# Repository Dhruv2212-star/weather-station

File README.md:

# Assembly image (what it will look like inside)

## Schematic (connections of the components)

## PCB tracings 

# What is this rediculous looking thing?? 
It is a really cheap and simple Weather station! it shows you data of your surrounding area such as temp, humidity, AQI  
i made it as a challenge to make a weather station that shows data not just on a LCD but on your phone from YOUR surrounding, not some  
sensor miles away from your surrounding.  
# Firmware 
since this uses ESP32, simply flash the firmware onto the board 
# ussage
connect it to the Wifi and you should be able to be see the data as a webpage on it's IP.  

# BOM 
| Reference | Qty | Value | DNP | Exclude from BOM | Exclude from Board | Footprint | Datasheet |
|---|---:|---|---|---|---|---|---|
| C1,C2 | 2 | 4.7 µF | | | | Capacitor_SMD:C_0805_2012Metric | |
| C3,C4,C5,C6 | 4 | 10 µF | | | | Capacitor_SMD:C_0805_2012Metric | |
| D1 | 1 | STATUS LED | | | | LED_THT:LED_D5.0mm | |
| J1 | 1 | USB_C_Receptacle_USB2.0_16P | | | | Connector_USB:USB_C_Receptacle_GCT_USB4105-xx-A_16P_TopMnt_Horizontal | [USB Type-C Specification](https://www.usb.org/sites/default/files/documents/usb_type-c.zip) |
| J2 | 1 | TPS61023 | | | | Connector_PinHeader_2.54mm:PinHeader_1x04_P2.54mm_Vertical | |
| J3 | 1 | Battery | | | | Connector_PinHeader_2.54mm:PinHeader_1x02_P2.54mm_Vertical | |
| J4 | 1 | BME280 | | | | Connector_PinHeader_2.54mm:PinHeader_1x04_P2.54mm_Vertical | |
| J5 | 1 | PMS5003 | | | | Connector_JST:JST_GH_BM08B-GHS-TBT_1x08-1MP_P1.25mm_Vertical | |
| R1 | 1 | 330 Ω | | | | Resistor_THT:R_Axial_DIN0207_L6.3mm_D2.5mm_P10.16mm_Horizontal | |
| R2 | 1 | 2 kΩ | | | | Resistor_SMD:R_0805_2012Metric | |
| R3,R4 | 2 | 5.1 kΩ | | | | Resistor_SMD:R_0805_2012Metric | |
| SW1,SW2,SW3 | 3 | SW_Push | | | | Button_Switch_THT:SW_PUSH_6mm | |
| U1 | 1 | ESP32-WROOM-32 | | | | ESP32 symbol and footprint:MODULE_ESP32-DEVKITC | [ESP32-WROOM-32 Datasheet](https://www.espressif.com/sites/default/files/documentation/esp32-wroom-32_datasheet_en.pdf) |
| U2 | 1 | MCP73831-2-OT | | | | Package_TO_SOT_SMD:SOT-23-5 | [MCP73831 Datasheet](http://ww1.microchip.com/downloads/en/DeviceDoc/20001984g.pdf) |
| U3 | 1 | AP2112K-3.3 | | | | Package_TO_SOT_SMD:SOT-23-5 | [AP2112K Datasheet](https://www.diodes.com/assets/Datasheets/AP2112.pdf) |

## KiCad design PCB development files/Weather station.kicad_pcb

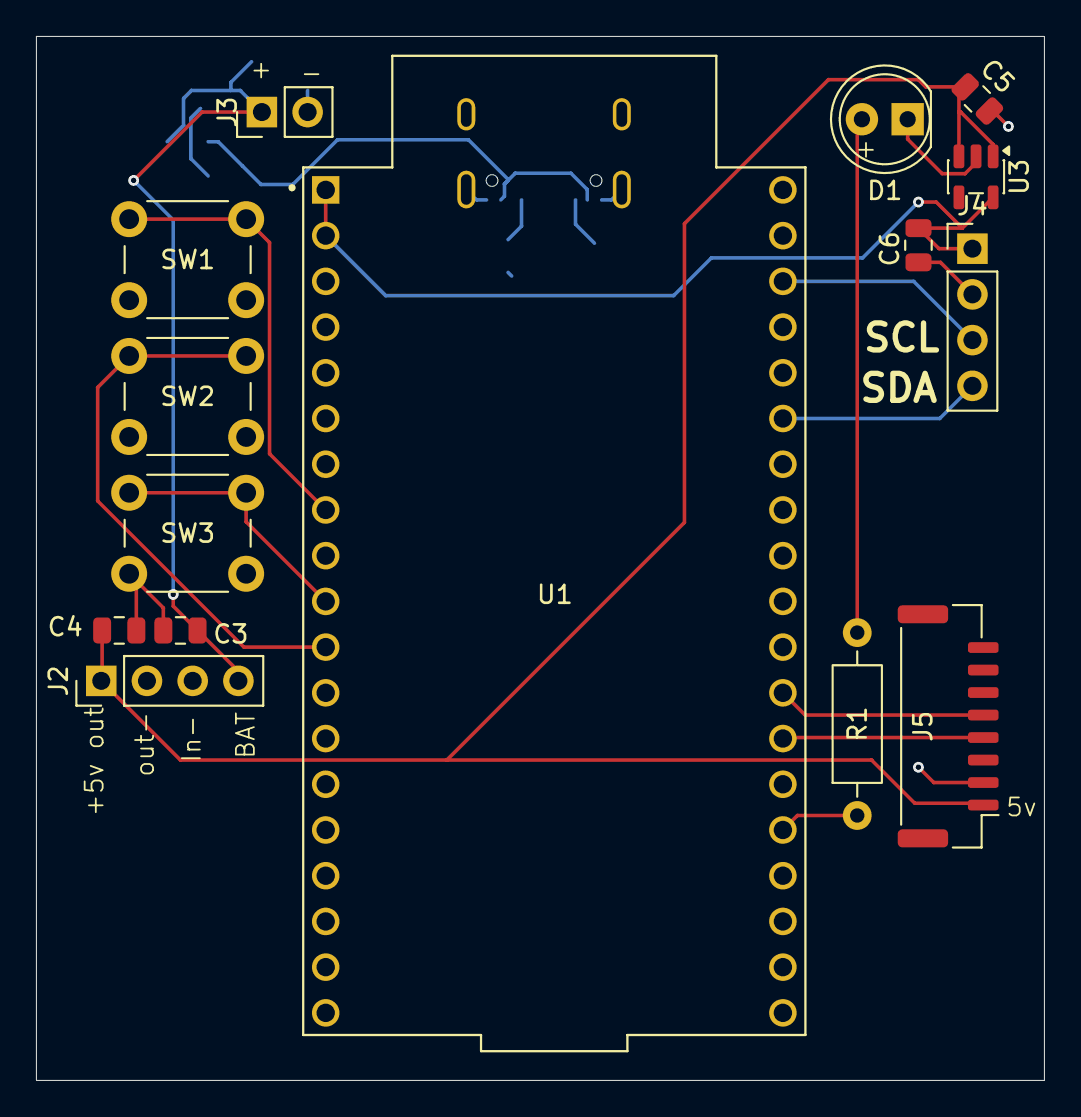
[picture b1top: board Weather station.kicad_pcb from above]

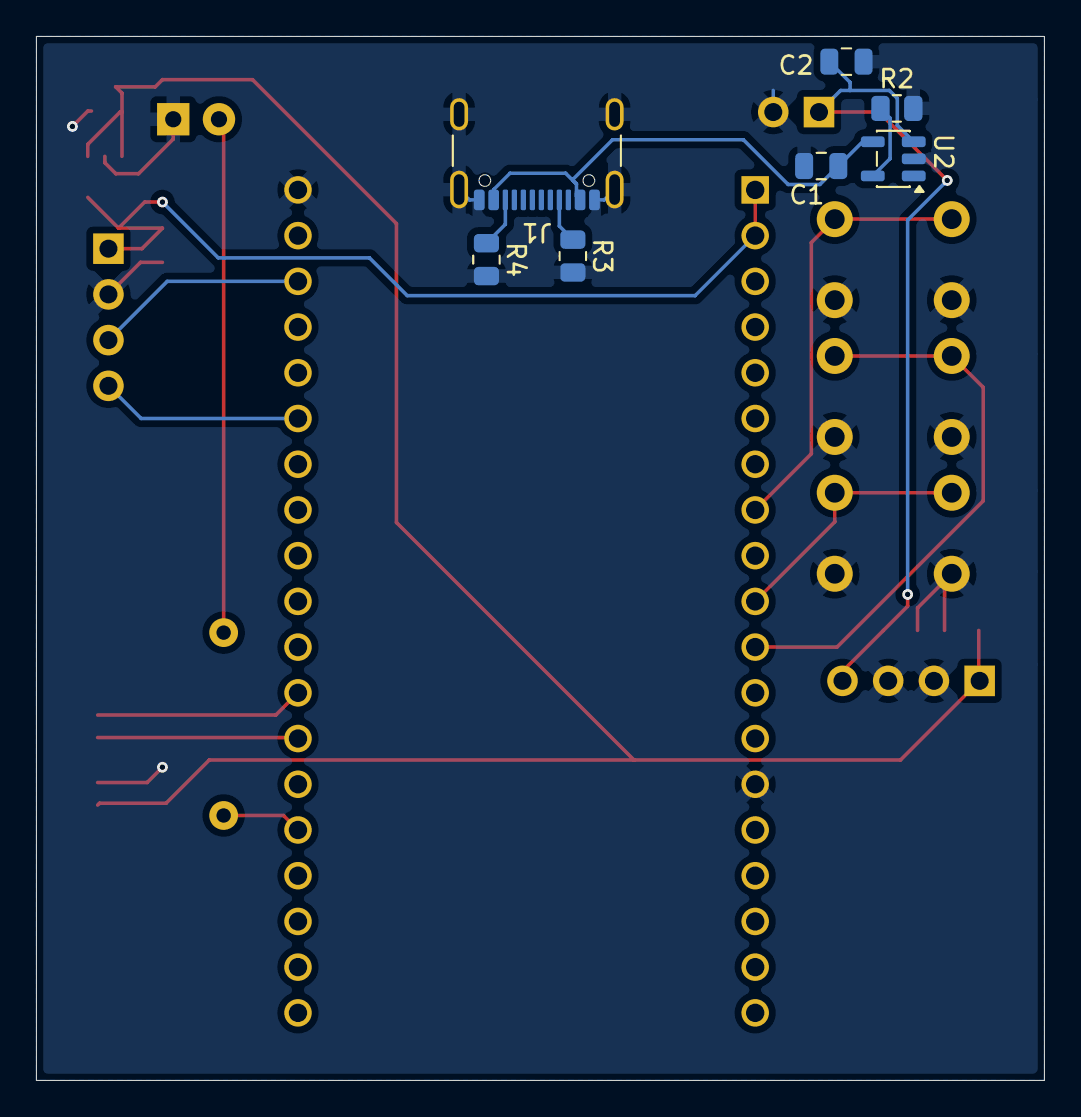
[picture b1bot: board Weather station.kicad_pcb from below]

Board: 2 copper layers, 56.0 x 58.0 mm, 22 parts (7 on the bottom side), 17 nets.

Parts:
C1, C2: 4.7 µF; C_0805_2012Metric
C3, C4, C5, C6: 10 µF; C_0805_2012Metric
D1: STATUS LED; LED_D5.0mm
J1: USB_C_Receptacle_USB2.0_16P; USB_C_Receptacle_GCT_USB4105-xx-A_16P_TopMnt_Horizontal
J2: TPS61023; PinHeader_1x04_P2.54mm_Vertical
J3: Battery; PinHeader_1x02_P2.54mm_Vertical
J4: BME280; PinHeader_1x04_P2.54mm_Vertical
J5: PMS5003; JST_GH_BM08B-GHS-TBT_1x08-1MP_P1.25mm_Vertical
R1: 330; R_Axial_DIN0207_L6.3mm_D2.5mm_P10.16mm_Horizontal
R2: 2 kΩ; R_0805_2012Metric
R3, R4: 5.1 kΩ; R_0805_2012Metric
SW1, SW2, SW3: SW_Push; SW_PUSH_6mm
U1: ESP32-WROOM-32; MODULE_ESP32-DEVKITC
U2: MCP73831-2-OT; SOT-23-5
U3: AP2112K-3.3; SOT-23-5

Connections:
+3V3: C6.1, J4.1, U1.1 (3V3), U1.2 (EN), U3.5 (VOUT)
+5V: C4.1, C5.2, J2.1, J5.1, U3.1 (VIN), U3.3 (EN)
/BAT+: C2.1, C3.1, J2.4, J3.1, U2.3 (V_{BAT})
/SCL: J4.3, U1.36 (IO22)
/SDA: J4.4, U1.33 (IO21)
/USB_5V: C1.1, J1.A4 (VBUS), J1.A9 (VBUS), J1.B4 (VBUS), J1.B9 (VBUS), U2.4 (V_{DD})
GND: C1.2, C2.2, C3.2, C4.2, C5.1, C6.2, D1.1 (K), J1.A1 (GND), J1.A12 (GND), J1.B1 (GND), J1.B12 (GND), J1.SH (SHIELD), J2.2, J2.3, J3.2, J4.2, J5.2, R2.2, R3.2, R4.2, SW1.2, SW2.2, SW3.2, U1.14 (GND1), U1.38 (GND3), U2.2 (V_{SS}), U3.2 (GND)
unnamed: D1.2 (A), R1.2
unnamed: J1.A5 (CC1), R3.1
unnamed: J1.B5 (CC2), R4.1
unnamed: J5.4, U1.26 (IO4)
unnamed: J5.5, U1.27 (IO16)
unnamed: R1.1, U1.24 (IO2)
unnamed: SW3.1, U1.10 (IO26)
unnamed: SW2.1, U1.11 (IO27)
unnamed: SW1.1, U1.8 (IO33)
unnamed: R2.1, U2.5 (PROG)
